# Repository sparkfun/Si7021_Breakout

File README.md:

SparkFun Humidity and Temperature Sensor Breakout - Si7021
===========================================================

[*SparkFun Humidity and Temperature Sensor Breakout - Si7021 (SEN-13763)*](https://www.sparkfun.com/products/13763)

This is a breadboard-friendly breakout board for the Si7021 temperature and humidiy sensor.

Repository Contents
-------------------
* **/Firmware** - Example code
* **/Hardware** - Eagle design files (.brd, .sch)
* **/Libraries** - Libraries for use with the Si7021
* **/Production** - Production panel files (.brd)

Documentation
--------------
* **[Library](https://github.com/sparkfun/SparkFun_Si701_Breakout_Arduino_Library)** - Arduino library for the Si7021.
* **[Hookup Guide](https://learn.sparkfun.com/tutorials/si7021-humidity-and-temperature-sensor-hookup-guide)** - Basic hookup guide for the Si7021.
* **[SparkFun Fritzing repo](https://github.com/sparkfun/Fritzing_Parts)** - Fritzing diagrams for SparkFun products.
* **[SparkFun 3D Model repo](https://github.com/sparkfun/3D_Models)** - 3D models of SparkFun products.

License Information
-------------------

This product is _**open source**_!

Please review the LICENSE.md file for license information.

If you have any questions or concerns on licensing, please contact techsupport@sparkfun.com.

Distributed as-is; no warranty is given.

- Your friends at SparkFun.

_<COLLABORATION CREDIT>_

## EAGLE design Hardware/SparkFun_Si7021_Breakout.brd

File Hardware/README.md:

SparkFun <PRODUCT NAME> Design Files
=====================================

The .sch and .brd files hare are Eagle CAD schematic and PCB design files from SparkFun Electronics.
A freeware version of Eagle can be found [here](http://www.cadsoftusa.com/download-eagle/freeware/). 

License Information
-------------------

This product is _**open source**_!

Please review the LICENSE.md file for license information.

If you have any questions or concerns on licensing, please contact techsupport@sparkfun.com.

Distributed as-is; no warranty is given.

- Your friends at SparkFun.

_<COLLABORATION CREDIT>_

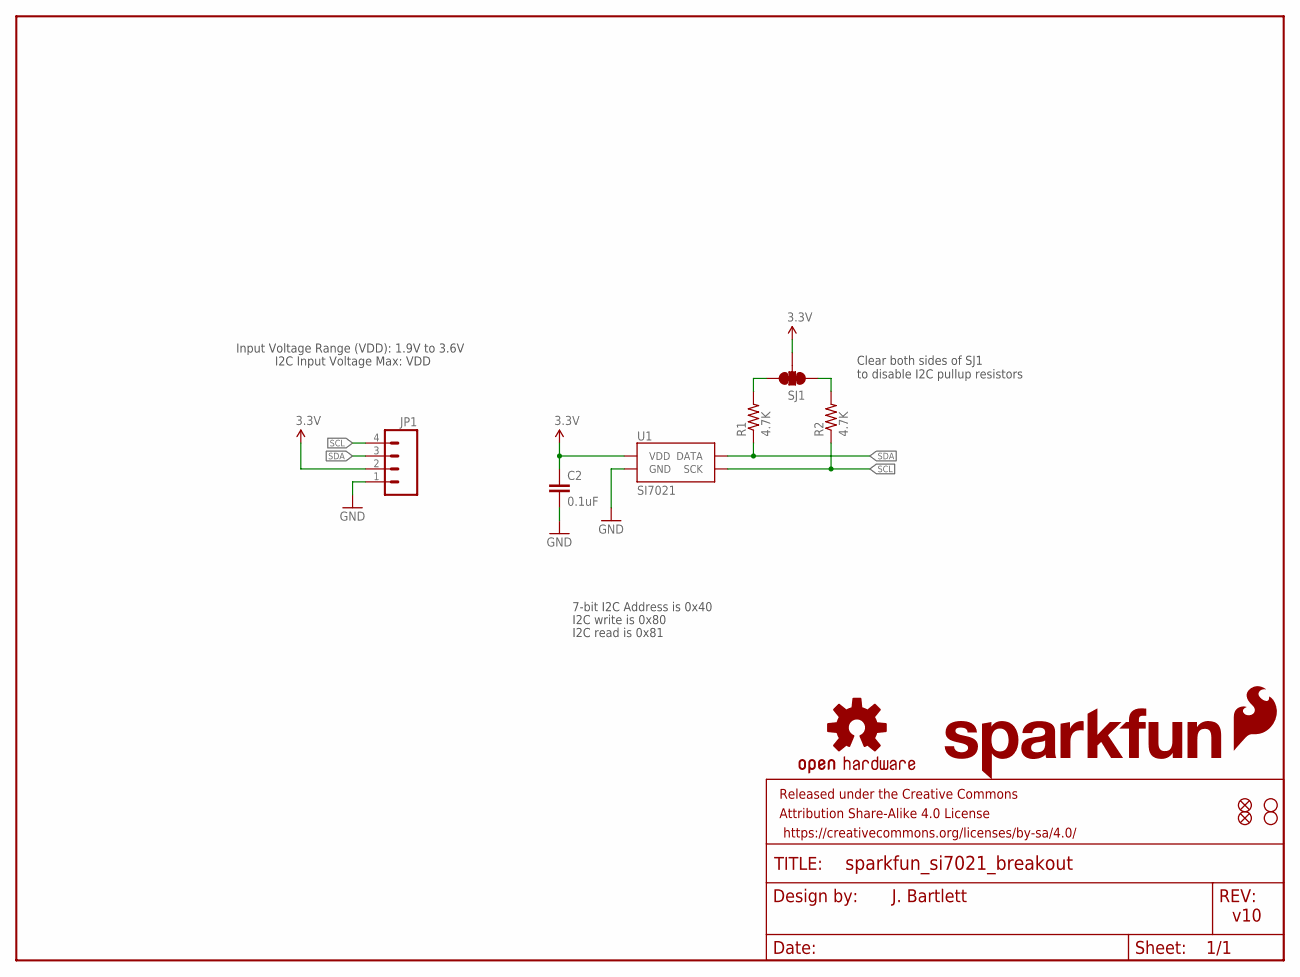
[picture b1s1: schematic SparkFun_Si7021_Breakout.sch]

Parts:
C2: 0.1uF; 0603-CAP
FRAME2: FRAME-LETTER; CREATIVE_COMMONS
JP1: M04PTH; 1X04
JP3, JP4: FIDUCIALUFIDUCIAL; MICRO-FIDUCIAL
LOGO2: OSHW-LOGOS; OSHW-LOGO-S
LOGO3: SFE_LOGO_FLAME.1_INCH; SFE_LOGO_FLAME_.1
LOGO4: SFE_LOGO_NAME.1_INCH; SFE_LOGO_NAME_.1
R1, R2: 4.7K; 0603-RES
SJ1: SOLDERJUMPER_2WAYPASTE1&2&3; SJ_3_PASTE1&2&3
STANDOFF1, STANDOFF2: STAND-OFF
U1: SI7021

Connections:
3.3V: C2.1, JP1.2, SJ1.2, U1.VDD
GND: C2.2, JP1.1, U1.GND
unnamed: R1.2, SJ1.3
unnamed: R2.2, SJ1.1
SCL: JP1.4, R2.1, U1.SCK
SDA: JP1.3, R1.1, U1.DATA

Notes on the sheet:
J. Bartlett
Clear both sides of SJ1 to disable I2C pullup resistors
7-bit I2C Address is 0x40
I2C write is 0x80
I2C read is 0x81
v10
Input Voltage Range (VDD): 1.9V to 3.6V
I2C Input Voltage Max: VDD

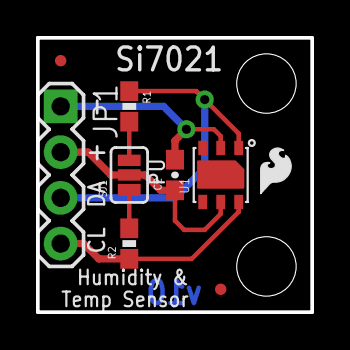
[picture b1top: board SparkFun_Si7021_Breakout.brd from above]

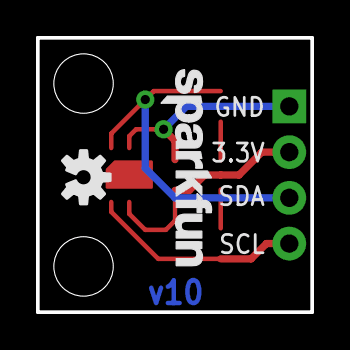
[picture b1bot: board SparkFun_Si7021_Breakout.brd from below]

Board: 2 copper layers, 15.2 x 15.2 mm, 14 parts (2 on the bottom side), 6 nets.

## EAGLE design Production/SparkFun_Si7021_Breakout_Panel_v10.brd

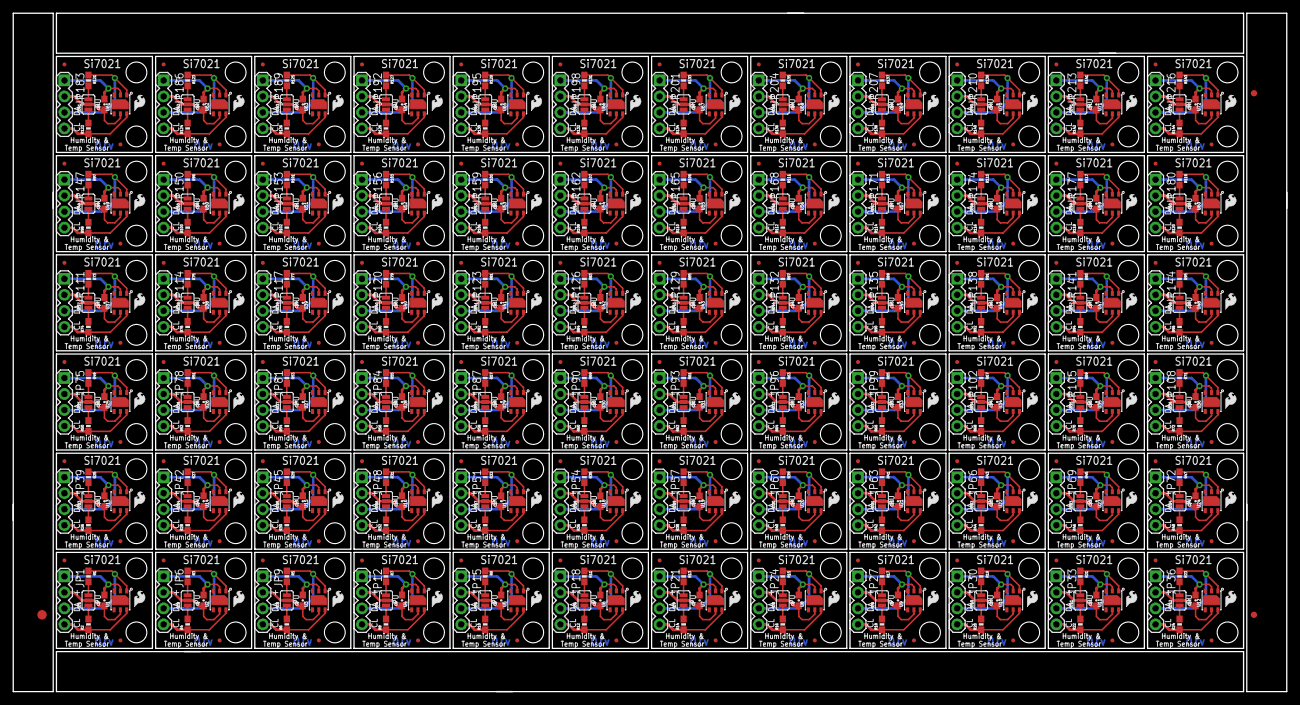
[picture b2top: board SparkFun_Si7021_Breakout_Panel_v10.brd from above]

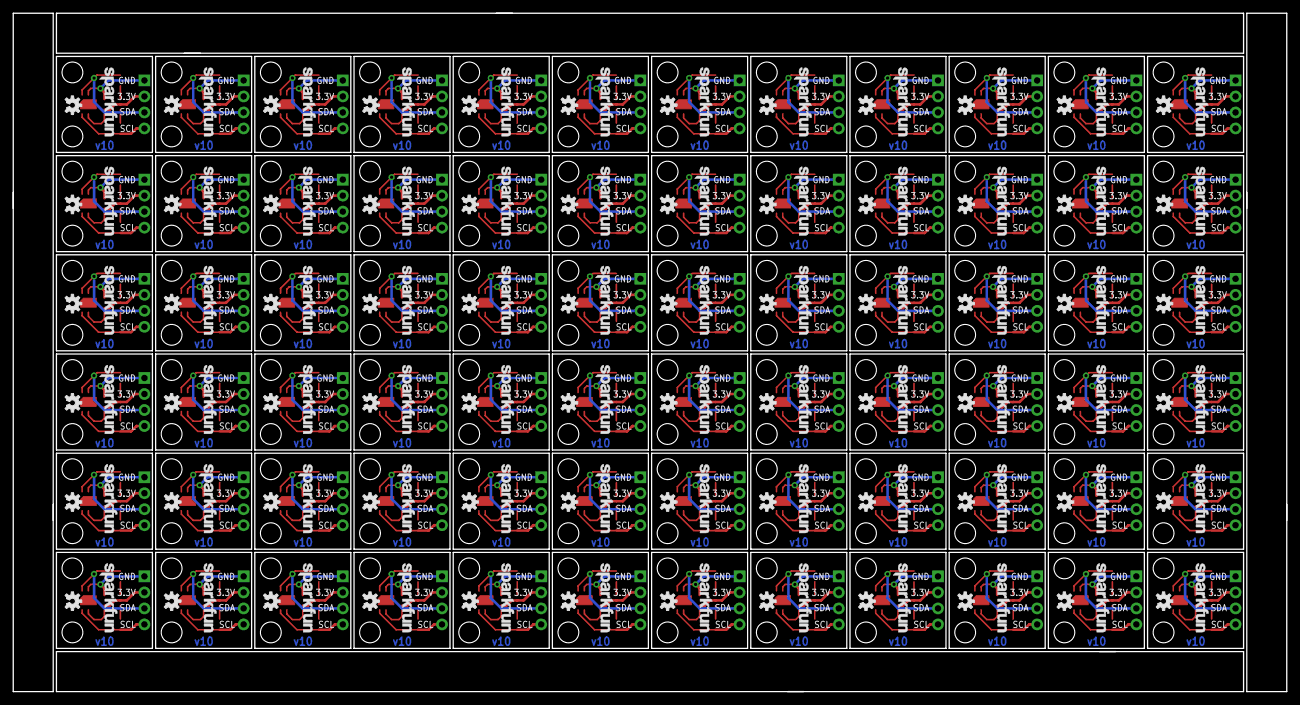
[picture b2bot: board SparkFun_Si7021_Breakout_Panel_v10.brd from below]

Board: 2 copper layers, 202.2 x 107.7 mm, 939 parts (144 on the bottom side), 432 nets.

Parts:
C1, C2, C3, C4, C5, C6, C7, C8, C9, C10, C11, C12, C13, C14, C15, C16, C17, C18, C19, C20, C21, C22, C23, C24, C25, C26, C27, C28, C29, C30, C31, C32, C33, C34, C35, C36, C37, C38, C39, C40, C41, C42, C43, C44, C45, C46, C47, C48, C49, C50, C51, C52, C53, C54, C55, C56, C57, C58, C59, C60, C61, C62, C63, C64, C65, C66, C67, C68, C69, C70, C71, C72: 0.1uF; 0603-CAP
E$1: FIDUCIAL-1.5X3
E$5, E$6: FIDUCIAL-1X2
JP1, JP6, JP9, JP12, JP15, JP18, JP21, JP24, JP27, JP30, JP33, JP36, JP39, JP42, JP45, JP48, JP51, JP54, JP57, JP60, JP63, JP66, JP69, JP72, JP75, JP78, JP81, JP84, JP87, JP90, JP93, JP96, JP99, JP102, JP105, JP108, JP111, JP114, JP117, JP120, JP123, JP126, JP129, JP132, JP135, JP138, JP141, JP144, JP147, JP150, JP153, JP156, JP159, JP162, JP165, JP168, JP171, JP174, JP177, JP180, JP183, JP186, JP189, JP192, JP195, JP198, JP201, JP204, JP207, JP210, JP213, JP216: 1X04
JP2, JP3, JP4, JP5, JP7, JP8, JP10, JP11, JP13, JP14, JP16, JP17, JP19, JP20, JP22, JP23, JP25, JP26, JP28, JP29, JP31, JP32, JP34, JP35, JP37, JP38, JP40, JP41, JP43, JP44, JP46, JP47, JP49, JP50, JP52, JP53, JP55, JP56, JP58, JP59, JP61, JP62, JP64, JP65, JP67, JP68, JP70, JP71, JP73, JP74, JP76, JP77, JP79, JP80, JP82, JP83, JP85, JP86, JP88, JP89, JP91, JP92, JP94, JP95, JP97, JP98, JP100, JP101, JP103, JP104, JP106, JP107, JP109, JP110, JP112, JP113, JP115, JP116, JP118, JP119, JP121, JP122, JP124, JP125, JP127, JP128, JP130, JP131, JP133, JP134, JP136, JP137, JP139, JP140, JP142, JP143, JP145, JP146, JP148, JP149, JP151, JP152, JP154, JP155, JP157, JP158, JP160, JP161, JP163, JP164, JP166, JP167, JP169, JP170, JP172, JP173, JP175, JP176, JP178, JP179, JP181, JP182, JP184, JP185, JP187, JP188, JP190, JP191, JP193, JP194, JP196, JP197, JP199, JP200, JP202, JP203, JP205, JP206, JP208, JP209, JP211, JP212, JP214, JP215: FIDUCIALUFIDUCIAL; MICRO-FIDUCIAL
LOGO1, LOGO2, LOGO7, LOGO10, LOGO13, LOGO16, LOGO19, LOGO22, LOGO25, LOGO28, LOGO31, LOGO34, LOGO37, LOGO40, LOGO43, LOGO46, LOGO49, LOGO52, LOGO55, LOGO58, LOGO61, LOGO64, LOGO67, LOGO70, LOGO73, LOGO76, LOGO79, LOGO82, LOGO85, LOGO88, LOGO91, LOGO94, LOGO97, LOGO100, LOGO103, LOGO106, LOGO109, LOGO112, LOGO115, LOGO118, LOGO121, LOGO124, LOGO127, LOGO130, LOGO133, LOGO136, LOGO139, LOGO142, LOGO145, LOGO148, LOGO151, LOGO154, LOGO157, LOGO160, LOGO163, LOGO166, LOGO169, LOGO172, LOGO175, LOGO178, LOGO181, LOGO184, LOGO187, LOGO190, LOGO193, LOGO196, LOGO199, LOGO202, LOGO205, LOGO208, LOGO211, LOGO214: OSHW-LOGOS; OSHW-LOGO-S
LOGO3, LOGO5, LOGO8, LOGO11, LOGO14, LOGO17, LOGO20, LOGO23, LOGO26, LOGO29, LOGO32, LOGO35, LOGO38, LOGO41, LOGO44, LOGO47, LOGO50, LOGO53, LOGO56, LOGO59, LOGO62, LOGO65, LOGO68, LOGO71, LOGO74, LOGO77, LOGO80, LOGO83, LOGO86, LOGO89, LOGO92, LOGO95, LOGO98, LOGO101, LOGO104, LOGO107, LOGO110, LOGO113, LOGO116, LOGO119, LOGO122, LOGO125, LOGO128, LOGO131, LOGO134, LOGO137, LOGO140, LOGO143, LOGO146, LOGO149, LOGO152, LOGO155, LOGO158, LOGO161, LOGO164, LOGO167, LOGO170, LOGO173, LOGO176, LOGO179, LOGO182, LOGO185, LOGO188, LOGO191, LOGO194, LOGO197, LOGO200, LOGO203, LOGO206, LOGO209, LOGO212, LOGO215: SFE_LOGO_FLAME.1_INCH; SFE_LOGO_FLAME_.1
LOGO4, LOGO6, LOGO9, LOGO12, LOGO15, LOGO18, LOGO21, LOGO24, LOGO27, LOGO30, LOGO33, LOGO36, LOGO39, LOGO42, LOGO45, LOGO48, LOGO51, LOGO54, LOGO57, LOGO60, LOGO63, LOGO66, LOGO69, LOGO72, LOGO75, LOGO78, LOGO81, LOGO84, LOGO87, LOGO90, LOGO93, LOGO96, LOGO99, LOGO102, LOGO105, LOGO108, LOGO111, LOGO114, LOGO117, LOGO120, LOGO123, LOGO126, LOGO129, LOGO132, LOGO135, LOGO138, LOGO141, LOGO144, LOGO147, LOGO150, LOGO153, LOGO156, LOGO159, LOGO162, LOGO165, LOGO168, LOGO171, LOGO174, LOGO177, LOGO180, LOGO183, LOGO186, LOGO189, LOGO192, LOGO195, LOGO198, LOGO201, LOGO204, LOGO207, LOGO210, LOGO213, LOGO216: SFE_LOGO_NAME.1_INCH; SFE_LOGO_NAME_.1
R1, R2, R3, R4, R5, R6, R7, R8, R9, R10, R11, R12, R13, R14, R15, R16, R17, R18, R19, R20, R21, R22, R23, R24, R25, R26, R27, R28, R29, R30, R31, R32, R33, R34, R35, R36, R37, R38, R39, R40, R41, R42, R43, R44, R45, R46, R47, R48, R49, R50, R51, R52, R53, R54, R55, R56, R57, R58, R59, R60, R61, R62, R63, R64, R65, R66, R67, R68, R69, R70, R71, R72, R73, R74, R75, R76, R77, R78, R79, R80, R81, R82, R83, R84, R85, R86, R87, R88, R89, R90, R91, R92, R93, R94, R95, R96, R97, R98, R99, R100, R101, R102, R103, R104, R105, R106, R107, R108, R109, R110, R111, R112, R113, R114, R115, R116, R117, R118, R119, R120, R121, R122, R123, R124, R125, R126, R127, R128, R129, R130, R131, R132, R133, R134, R135, R136, R137, R138, R139, R140, R141, R142, R143, R144: 4.7K; 0603-RES
SJ1, SJ2, SJ3, SJ4, SJ5, SJ6, SJ7, SJ8, SJ9, SJ10, SJ11, SJ12, SJ13, SJ14, SJ15, SJ16, SJ17, SJ18, SJ19, SJ20, SJ21, SJ22, SJ23, SJ24, SJ25, SJ26, SJ27, SJ28, SJ29, SJ30, SJ31, SJ32, SJ33, SJ34, SJ35, SJ36, SJ37, SJ38, SJ39, SJ40, SJ41, SJ42, SJ43, SJ44, SJ45, SJ46, SJ47, SJ48, SJ49, SJ50, SJ51, SJ52, SJ53, SJ54, SJ55, SJ56, SJ57, SJ58, SJ59, SJ60, SJ61, SJ62, SJ63, SJ64, SJ65, SJ66, SJ67, SJ68, SJ69, SJ70, SJ71, SJ72: SJ_3_PASTE1&2&3
STANDOFF1, STANDOFF2, STANDOFF3, STANDOFF4, STANDOFF5, STANDOFF6, STANDOFF7, STANDOFF8, STANDOFF9, STANDOFF10, STANDOFF11, STANDOFF12, STANDOFF13, STANDOFF14, STANDOFF15, STANDOFF16, STANDOFF17, STANDOFF18, STANDOFF19, STANDOFF20, STANDOFF21, STANDOFF22, STANDOFF23, STANDOFF24, STANDOFF25, STANDOFF26, STANDOFF27, STANDOFF28, STANDOFF29, STANDOFF30, STANDOFF31, STANDOFF32, STANDOFF33, STANDOFF34, STANDOFF35, STANDOFF36, STANDOFF37, STANDOFF38, STANDOFF39, STANDOFF40, STANDOFF41, STANDOFF42, STANDOFF43, STANDOFF44, STANDOFF45, STANDOFF46, STANDOFF47, STANDOFF48, STANDOFF49, STANDOFF50, STANDOFF51, STANDOFF52, STANDOFF53, STANDOFF54, STANDOFF55, STANDOFF56, STANDOFF57, STANDOFF58, STANDOFF59, STANDOFF60, STANDOFF61, STANDOFF62, STANDOFF63, STANDOFF64, STANDOFF65, STANDOFF66, STANDOFF67, STANDOFF68, STANDOFF69, STANDOFF70, STANDOFF71, STANDOFF72, STANDOFF73, STANDOFF74, STANDOFF75, STANDOFF76, STANDOFF77, STANDOFF78, STANDOFF79, STANDOFF80, STANDOFF81, STANDOFF82, STANDOFF83, STANDOFF84, STANDOFF85, STANDOFF86, STANDOFF87, STANDOFF88, STANDOFF89, STANDOFF90, STANDOFF91, STANDOFF92, STANDOFF93, STANDOFF94, STANDOFF95, STANDOFF96, STANDOFF97, STANDOFF98, STANDOFF99, STANDOFF100, STANDOFF101, STANDOFF102, STANDOFF103, STANDOFF104, STANDOFF105, STANDOFF106, STANDOFF107, STANDOFF108, STANDOFF109, STANDOFF110, STANDOFF111, STANDOFF112, STANDOFF113, STANDOFF114, STANDOFF115, STANDOFF116, STANDOFF117, STANDOFF118, STANDOFF119, STANDOFF120, STANDOFF121, STANDOFF122, STANDOFF123, STANDOFF124, STANDOFF125, STANDOFF126, STANDOFF127, STANDOFF128, STANDOFF129, STANDOFF130, STANDOFF131, STANDOFF132, STANDOFF133, STANDOFF134, STANDOFF135, STANDOFF136, STANDOFF137, STANDOFF138, STANDOFF139, STANDOFF140, STANDOFF141, STANDOFF142, STANDOFF143, STANDOFF144: STAND-OFF
U1, U2, U3, U4, U5, U6, U7, U8, U9, U10, U11, U12, U13, U14, U15, U16, U17, U18, U19, U20, U21, U22, U23, U24, U25, U26, U27, U28, U29, U30, U31, U32, U33, U34, U35, U36, U37, U38, U39, U40, U41, U42, U43, U44, U45, U46, U47, U48, U49, U50, U51, U52, U53, U54, U55, U56, U57, U58, U59, U60, U61, U62, U63, U64, U65, U66, U67, U68, U69, U70, U71, U72: SI7021

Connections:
3.3V: C2.1, JP1.2, SJ1.2, U1.VDD
3.3V1: C1.1, JP6.2, SJ2.2, U2.VDD
3.3V2: C3.1, JP9.2, SJ3.2, U3.VDD
3.3V3: C4.1, JP12.2, SJ4.2, U4.VDD
3.3V4: C5.1, JP15.2, SJ5.2, U5.VDD
3.3V5: C6.1, JP18.2, SJ6.2, U6.VDD
3.3V6: C7.1, JP21.2, SJ7.2, U7.VDD
3.3V7: C8.1, JP24.2, SJ8.2, U8.VDD
3.3V8: C9.1, JP27.2, SJ9.2, U9.VDD
3.3V9: C10.1, JP30.2, SJ10.2, U10.VDD
3.3V10: C11.1, JP33.2, SJ11.2, U11.VDD
3.3V11: C12.1, JP36.2, SJ12.2, U12.VDD
3.3V12: C13.1, JP39.2, SJ13.2, U13.VDD
3.3V13: C14.1, JP42.2, SJ14.2, U14.VDD
3.3V14: C15.1, JP45.2, SJ15.2, U15.VDD
3.3V15: C16.1, JP48.2, SJ16.2, U16.VDD
3.3V16: C17.1, JP51.2, SJ17.2, U17.VDD
3.3V17: C18.1, JP54.2, SJ18.2, U18.VDD
3.3V18: C19.1, JP57.2, SJ19.2, U19.VDD
3.3V19: C20.1, JP60.2, SJ20.2, U20.VDD
3.3V20: C21.1, JP63.2, SJ21.2, U21.VDD
3.3V21: C22.1, JP66.2, SJ22.2, U22.VDD
3.3V22: C23.1, JP69.2, SJ23.2, U23.VDD
3.3V23: C24.1, JP72.2, SJ24.2, U24.VDD
3.3V24: C25.1, JP75.2, SJ25.2, U25.VDD
3.3V25: C26.1, JP78.2, SJ26.2, U26.VDD
3.3V26: C27.1, JP81.2, SJ27.2, U27.VDD
3.3V27: C28.1, JP84.2, SJ28.2, U28.VDD
3.3V28: C29.1, JP87.2, SJ29.2, U29.VDD
3.3V29: C30.1, JP90.2, SJ30.2, U30.VDD
3.3V30: C31.1, JP93.2, SJ31.2, U31.VDD
3.3V31: C32.1, JP96.2, SJ32.2, U32.VDD
3.3V32: C33.1, JP99.2, SJ33.2, U33.VDD
3.3V33: C34.1, JP102.2, SJ34.2, U34.VDD
3.3V34: C35.1, JP105.2, SJ35.2, U35.VDD
3.3V35: C36.1, JP108.2, SJ36.2, U36.VDD
3.3V36: C37.1, JP111.2, SJ37.2, U37.VDD
3.3V37: C38.1, JP114.2, SJ38.2, U38.VDD
3.3V38: C39.1, JP117.2, SJ39.2, U39.VDD
3.3V39: C40.1, JP120.2, SJ40.2, U40.VDD
3.3V40: C41.1, JP123.2, SJ41.2, U41.VDD
3.3V41: C42.1, JP126.2, SJ42.2, U42.VDD
3.3V42: C43.1, JP129.2, SJ43.2, U43.VDD
3.3V43: C44.1, JP132.2, SJ44.2, U44.VDD
3.3V44: C45.1, JP135.2, SJ45.2, U45.VDD
3.3V45: C46.1, JP138.2, SJ46.2, U46.VDD
3.3V46: C47.1, JP141.2, SJ47.2, U47.VDD
3.3V47: C48.1, JP144.2, SJ48.2, U48.VDD
3.3V48: C49.1, JP147.2, SJ49.2, U49.VDD
3.3V49: C50.1, JP150.2, SJ50.2, U50.VDD
3.3V50: C51.1, JP153.2, SJ51.2, U51.VDD
3.3V51: C52.1, JP156.2, SJ52.2, U52.VDD
3.3V52: C53.1, JP159.2, SJ53.2, U53.VDD
3.3V53: C54.1, JP162.2, SJ54.2, U54.VDD
3.3V54: C55.1, JP165.2, SJ55.2, U55.VDD
3.3V55: C56.1, JP168.2, SJ56.2, U56.VDD
3.3V56: C57.1, JP171.2, SJ57.2, U57.VDD
3.3V57: C58.1, JP174.2, SJ58.2, U58.VDD
3.3V58: C59.1, JP177.2, SJ59.2, U59.VDD
3.3V59: C60.1, JP180.2, SJ60.2, U60.VDD
3.3V60: C61.1, JP183.2, SJ61.2, U61.VDD
3.3V61: C62.1, JP186.2, SJ62.2, U62.VDD
3.3V62: C63.1, JP189.2, SJ63.2, U63.VDD
3.3V63: C64.1, JP192.2, SJ64.2, U64.VDD
3.3V64: C65.1, JP195.2, SJ65.2, U65.VDD
3.3V65: C66.1, JP198.2, SJ66.2, U66.VDD
3.3V66: C67.1, JP201.2, SJ67.2, U67.VDD
3.3V67: C68.1, JP204.2, SJ68.2, U68.VDD
3.3V68: C69.1, JP207.2, SJ69.2, U69.VDD
3.3V69: C70.1, JP210.2, SJ70.2, U70.VDD
3.3V70: C71.1, JP213.2, SJ71.2, U71.VDD
3.3V71: C72.1, JP216.2, SJ72.2, U72.VDD
GND: C2.2, JP1.1, U1.GND
GND1: C1.2, JP6.1, U2.GND
GND2: C3.2, JP9.1, U3.GND
GND3: C4.2, JP12.1, U4.GND
GND4: C5.2, JP15.1, U5.GND
GND5: C6.2, JP18.1, U6.GND
GND6: C7.2, JP21.1, U7.GND
GND7: C8.2, JP24.1, U8.GND
GND8: C9.2, JP27.1, U9.GND
GND9: C10.2, JP30.1, U10.GND
GND10: C11.2, JP33.1, U11.GND
GND11: C12.2, JP36.1, U12.GND
GND12: C13.2, JP39.1, U13.GND
GND13: C14.2, JP42.1, U14.GND
GND14: C15.2, JP45.1, U15.GND
GND15: C16.2, JP48.1, U16.GND
GND16: C17.2, JP51.1, U17.GND
GND17: C18.2, JP54.1, U18.GND
GND18: C19.2, JP57.1, U19.GND
GND19: C20.2, JP60.1, U20.GND
GND20: C21.2, JP63.1, U21.GND
GND21: C22.2, JP66.1, U22.GND
GND22: C23.2, JP69.1, U23.GND
GND23: C24.2, JP72.1, U24.GND
GND24: C25.2, JP75.1, U25.GND
GND25: C26.2, JP78.1, U26.GND
GND26: C27.2, JP81.1, U27.GND
GND27: C28.2, JP84.1, U28.GND
GND28: C29.2, JP87.1, U29.GND
GND29: C30.2, JP90.1, U30.GND
GND30: C31.2, JP93.1, U31.GND
GND31: C32.2, JP96.1, U32.GND
GND32: C33.2, JP99.1, U33.GND
GND33: C34.2, JP102.1, U34.GND
GND34: C35.2, JP105.1, U35.GND
GND35: C36.2, JP108.1, U36.GND
GND36: C37.2, JP111.1, U37.GND
GND37: C38.2, JP114.1, U38.GND
GND38: C39.2, JP117.1, U39.GND
GND39: C40.2, JP120.1, U40.GND
GND40: C41.2, JP123.1, U41.GND
GND41: C42.2, JP126.1, U42.GND
GND42: C43.2, JP129.1, U43.GND
GND43: C44.2, JP132.1, U44.GND
GND44: C45.2, JP135.1, U45.GND
GND45: C46.2, JP138.1, U46.GND
GND46: C47.2, JP141.1, U47.GND
GND47: C48.2, JP144.1, U48.GND
GND48: C49.2, JP147.1, U49.GND
GND49: C50.2, JP150.1, U50.GND
GND50: C51.2, JP153.1, U51.GND
GND51: C52.2, JP156.1, U52.GND
GND52: C53.2, JP159.1, U53.GND
GND53: C54.2, JP162.1, U54.GND
GND54: C55.2, JP165.1, U55.GND
GND55: C56.2, JP168.1, U56.GND
GND56: C57.2, JP171.1, U57.GND
GND57: C58.2, JP174.1, U58.GND
GND58: C59.2, JP177.1, U59.GND
GND59: C60.2, JP180.1, U60.GND
GND60: C61.2, JP183.1, U61.GND
GND61: C62.2, JP186.1, U62.GND
GND62: C63.2, JP189.1, U63.GND
GND63: C64.2, JP192.1, U64.GND
GND64: C65.2, JP195.1, U65.GND
GND65: C66.2, JP198.1, U66.GND
GND66: C67.2, JP201.1, U67.GND
GND67: C68.2, JP204.1, U68.GND
GND68: C69.2, JP207.1, U69.GND
GND69: C70.2, JP210.1, U70.GND
GND70: C71.2, JP213.1, U71.GND
GND71: C72.2, JP216.1, U72.GND
unnamed: R1.2, SJ1.3
unnamed: R2.2, SJ1.1
unnamed: R3.2, SJ2.3
unnamed: R4.2, SJ2.1
unnamed: R5.2, SJ3.3
unnamed: R6.2, SJ3.1
unnamed: R7.2, SJ4.3
unnamed: R8.2, SJ4.1
unnamed: R9.2, SJ5.3
unnamed: R10.2, SJ5.1
unnamed: R11.2, SJ6.3
unnamed: R12.2, SJ6.1
unnamed: R13.2, SJ7.3
unnamed: R14.2, SJ7.1
unnamed: R15.2, SJ8.3
unnamed: R16.2, SJ8.1
unnamed: R17.2, SJ9.3
unnamed: R18.2, SJ9.1
unnamed: R19.2, SJ10.3
unnamed: R20.2, SJ10.1
unnamed: R21.2, SJ11.3
unnamed: R22.2, SJ11.1
unnamed: R23.2, SJ12.3
unnamed: R24.2, SJ12.1
unnamed: R25.2, SJ13.3
unnamed: R26.2, SJ13.1
unnamed: R27.2, SJ14.3
unnamed: R28.2, SJ14.1
unnamed: R29.2, SJ15.3
unnamed: R30.2, SJ15.1
unnamed: R31.2, SJ16.3
unnamed: R32.2, SJ16.1
unnamed: R33.2, SJ17.3
unnamed: R34.2, SJ17.1
unnamed: R35.2, SJ18.3
unnamed: R36.2, SJ18.1
unnamed: R37.2, SJ19.3
unnamed: R38.2, SJ19.1
unnamed: R39.2, SJ20.3
unnamed: R40.2, SJ20.1
unnamed: R41.2, SJ21.3
unnamed: R42.2, SJ21.1
unnamed: R43.2, SJ22.3
unnamed: R44.2, SJ22.1
unnamed: R45.2, SJ23.3
unnamed: R46.2, SJ23.1
unnamed: R47.2, SJ24.3
unnamed: R48.2, SJ24.1
unnamed: R49.2, SJ25.3
unnamed: R50.2, SJ25.1
unnamed: R51.2, SJ26.3
unnamed: R52.2, SJ26.1
unnamed: R53.2, SJ27.3
unnamed: R54.2, SJ27.1
unnamed: R55.2, SJ28.3
unnamed: R56.2, SJ28.1
unnamed: R57.2, SJ29.3
unnamed: R58.2, SJ29.1
unnamed: R59.2, SJ30.3
unnamed: R60.2, SJ30.1
unnamed: R61.2, SJ31.3
unnamed: R62.2, SJ31.1
unnamed: R63.2, SJ32.3
unnamed: R64.2, SJ32.1
unnamed: R65.2, SJ33.3
unnamed: R66.2, SJ33.1
unnamed: R67.2, SJ34.3
unnamed: R68.2, SJ34.1
unnamed: R69.2, SJ35.3
unnamed: R70.2, SJ35.1
unnamed: R71.2, SJ36.3
unnamed: R72.2, SJ36.1
unnamed: R73.2, SJ37.3
unnamed: R74.2, SJ37.1
unnamed: R75.2, SJ38.3
unnamed: R76.2, SJ38.1
unnamed: R77.2, SJ39.3
unnamed: R78.2, SJ39.1
unnamed: R79.2, SJ40.3
unnamed: R80.2, SJ40.1
unnamed: R81.2, SJ41.3
unnamed: R82.2, SJ41.1
unnamed: R83.2, SJ42.3
unnamed: R84.2, SJ42.1
unnamed: R85.2, SJ43.3
unnamed: R86.2, SJ43.1
unnamed: R87.2, SJ44.3
unnamed: R88.2, SJ44.1
unnamed: R89.2, SJ45.3
unnamed: R90.2, SJ45.1
unnamed: R91.2, SJ46.3
unnamed: R92.2, SJ46.1
unnamed: R93.2, SJ47.3
unnamed: R94.2, SJ47.1
unnamed: R95.2, SJ48.3
unnamed: R96.2, SJ48.1
unnamed: R97.2, SJ49.3
unnamed: R98.2, SJ49.1
unnamed: R99.2, SJ50.3
unnamed: R100.2, SJ50.1
unnamed: R101.2, SJ51.3
unnamed: R102.2, SJ51.1
unnamed: R103.2, SJ52.3
unnamed: R104.2, SJ52.1
unnamed: R105.2, SJ53.3
unnamed: R106.2, SJ53.1
unnamed: R107.2, SJ54.3
unnamed: R108.2, SJ54.1
unnamed: R109.2, SJ55.3
unnamed: R110.2, SJ55.1
unnamed: R111.2, SJ56.3
unnamed: R112.2, SJ56.1
unnamed: R113.2, SJ57.3
unnamed: R114.2, SJ57.1
unnamed: R115.2, SJ58.3
unnamed: R116.2, SJ58.1
unnamed: R117.2, SJ59.3
unnamed: R118.2, SJ59.1
unnamed: R119.2, SJ60.3
unnamed: R120.2, SJ60.1
unnamed: R121.2, SJ61.3
unnamed: R122.2, SJ61.1
unnamed: R123.2, SJ62.3
unnamed: R124.2, SJ62.1
unnamed: R125.2, SJ63.3
unnamed: R126.2, SJ63.1
unnamed: R127.2, SJ64.3
unnamed: R128.2, SJ64.1
unnamed: R129.2, SJ65.3
unnamed: R130.2, SJ65.1
unnamed: R131.2, SJ66.3
unnamed: R132.2, SJ66.1
unnamed: R133.2, SJ67.3
unnamed: R134.2, SJ67.1
unnamed: R135.2, SJ68.3
unnamed: R136.2, SJ68.1
unnamed: R137.2, SJ69.3
unnamed: R138.2, SJ69.1
unnamed: R139.2, SJ70.3
unnamed: R140.2, SJ70.1
unnamed: R141.2, SJ71.3
unnamed: R142.2, SJ71.1
unnamed: R143.2, SJ72.3
unnamed: R144.2, SJ72.1
SCL: JP1.4, R2.1, U1.SCK
SCL1: JP6.4, R4.1, U2.SCK
SCL2: JP9.4, R6.1, U3.SCK
SCL3: JP12.4, R8.1, U4.SCK
SCL4: JP15.4, R10.1, U5.SCK
SCL5: JP18.4, R12.1, U6.SCK
SCL6: JP21.4, R14.1, U7.SCK
SCL7: JP24.4, R16.1, U8.SCK
SCL8: JP27.4, R18.1, U9.SCK
SCL9: JP30.4, R20.1, U10.SCK
SCL10: JP33.4, R22.1, U11.SCK
SCL11: JP36.4, R24.1, U12.SCK
SCL12: JP39.4, R26.1, U13.SCK
SCL13: JP42.4, R28.1, U14.SCK
SCL14: JP45.4, R30.1, U15.SCK
SCL15: JP48.4, R32.1, U16.SCK
SCL16: JP51.4, R34.1, U17.SCK
SCL17: JP54.4, R36.1, U18.SCK
SCL18: JP57.4, R38.1, U19.SCK
SCL19: JP60.4, R40.1, U20.SCK
SCL20: JP63.4, R42.1, U21.SCK
SCL21: JP66.4, R44.1, U22.SCK
SCL22: JP69.4, R46.1, U23.SCK
SCL23: JP72.4, R48.1, U24.SCK
SCL24: JP75.4, R50.1, U25.SCK
SCL25: JP78.4, R52.1, U26.SCK
SCL26: JP81.4, R54.1, U27.SCK
SCL27: JP84.4, R56.1, U28.SCK
SCL28: JP87.4, R58.1, U29.SCK
SCL29: JP90.4, R60.1, U30.SCK
SCL30: JP93.4, R62.1, U31.SCK
SCL31: JP96.4, R64.1, U32.SCK
SCL32: JP99.4, R66.1, U33.SCK
SCL33: JP102.4, R68.1, U34.SCK
SCL34: JP105.4, R70.1, U35.SCK
SCL35: JP108.4, R72.1, U36.SCK
SCL36: JP111.4, R74.1, U37.SCK
SCL37: JP114.4, R76.1, U38.SCK
SCL38: JP117.4, R78.1, U39.SCK
SCL39: JP120.4, R80.1, U40.SCK
SCL40: JP123.4, R82.1, U41.SCK
SCL41: JP126.4, R84.1, U42.SCK
SCL42: JP129.4, R86.1, U43.SCK
SCL43: JP132.4, R88.1, U44.SCK
SCL44: JP135.4, R90.1, U45.SCK
SCL45: JP138.4, R92.1, U46.SCK
SCL46: JP141.4, R94.1, U47.SCK
SCL47: JP144.4, R96.1, U48.SCK
SCL48: JP147.4, R98.1, U49.SCK
SCL49: JP150.4, R100.1, U50.SCK
SCL50: JP153.4, R102.1, U51.SCK
SCL51: JP156.4, R104.1, U52.SCK
SCL52: JP159.4, R106.1, U53.SCK
SCL53: JP162.4, R108.1, U54.SCK
SCL54: JP165.4, R110.1, U55.SCK
SCL55: JP168.4, R112.1, U56.SCK
SCL56: JP171.4, R114.1, U57.SCK
SCL57: JP174.4, R116.1, U58.SCK
SCL58: JP177.4, R118.1, U59.SCK
SCL59: JP180.4, R120.1, U60.SCK
SCL60: JP183.4, R122.1, U61.SCK
SCL61: JP186.4, R124.1, U62.SCK
SCL62: JP189.4, R126.1, U63.SCK
SCL63: JP192.4, R128.1, U64.SCK
SCL64: JP195.4, R130.1, U65.SCK
SCL65: JP198.4, R132.1, U66.SCK
SCL66: JP201.4, R134.1, U67.SCK
SCL67: JP204.4, R136.1, U68.SCK
SCL68: JP207.4, R138.1, U69.SCK
SCL69: JP210.4, R140.1, U70.SCK
SCL70: JP213.4, R142.1, U71.SCK
SCL71: JP216.4, R144.1, U72.SCK
SDA: JP1.3, R1.1, U1.DATA
SDA1: JP6.3, R3.1, U2.DATA
SDA2: JP9.3, R5.1, U3.DATA
SDA3: JP12.3, R7.1, U4.DATA
SDA4: JP15.3, R9.1, U5.DATA
SDA5: JP18.3, R11.1, U6.DATA
SDA6: JP21.3, R13.1, U7.DATA
SDA7: JP24.3, R15.1, U8.DATA
SDA8: JP27.3, R17.1, U9.DATA
SDA9: JP30.3, R19.1, U10.DATA
SDA10: JP33.3, R21.1, U11.DATA
SDA11: JP36.3, R23.1, U12.DATA
SDA12: JP39.3, R25.1, U13.DATA
SDA13: JP42.3, R27.1, U14.DATA
SDA14: JP45.3, R29.1, U15.DATA
SDA15: JP48.3, R31.1, U16.DATA
SDA16: JP51.3, R33.1, U17.DATA
SDA17: JP54.3, R35.1, U18.DATA
SDA18: JP57.3, R37.1, U19.DATA
SDA19: JP60.3, R39.1, U20.DATA
SDA20: JP63.3, R41.1, U21.DATA
SDA21: JP66.3, R43.1, U22.DATA
SDA22: JP69.3, R45.1, U23.DATA
SDA23: JP72.3, R47.1, U24.DATA
SDA24: JP75.3, R49.1, U25.DATA
SDA25: JP78.3, R51.1, U26.DATA
SDA26: JP81.3, R53.1, U27.DATA
SDA27: JP84.3, R55.1, U28.DATA
SDA28: JP87.3, R57.1, U29.DATA
SDA29: JP90.3, R59.1, U30.DATA
SDA30: JP93.3, R61.1, U31.DATA
SDA31: JP96.3, R63.1, U32.DATA
SDA32: JP99.3, R65.1, U33.DATA
SDA33: JP102.3, R67.1, U34.DATA
SDA34: JP105.3, R69.1, U35.DATA
SDA35: JP108.3, R71.1, U36.DATA
SDA36: JP111.3, R73.1, U37.DATA
SDA37: JP114.3, R75.1, U38.DATA
SDA38: JP117.3, R77.1, U39.DATA
SDA39: JP120.3, R79.1, U40.DATA
SDA40: JP123.3, R81.1, U41.DATA
SDA41: JP126.3, R83.1, U42.DATA
SDA42: JP129.3, R85.1, U43.DATA
SDA43: JP132.3, R87.1, U44.DATA
SDA44: JP135.3, R89.1, U45.DATA
SDA45: JP138.3, R91.1, U46.DATA
SDA46: JP141.3, R93.1, U47.DATA
SDA47: JP144.3, R95.1, U48.DATA
SDA48: JP147.3, R97.1, U49.DATA
SDA49: JP150.3, R99.1, U50.DATA
SDA50: JP153.3, R101.1, U51.DATA
SDA51: JP156.3, R103.1, U52.DATA
SDA52: JP159.3, R105.1, U53.DATA
SDA53: JP162.3, R107.1, U54.DATA
SDA54: JP165.3, R109.1, U55.DATA
SDA55: JP168.3, R111.1, U56.DATA
SDA56: JP171.3, R113.1, U57.DATA
SDA57: JP174.3, R115.1, U58.DATA
SDA58: JP177.3, R117.1, U59.DATA
SDA59: JP180.3, R119.1, U60.DATA
SDA60: JP183.3, R121.1, U61.DATA
SDA61: JP186.3, R123.1, U62.DATA
SDA62: JP189.3, R125.1, U63.DATA
SDA63: JP192.3, R127.1, U64.DATA
SDA64: JP195.3, R129.1, U65.DATA
SDA65: JP198.3, R131.1, U66.DATA
SDA66: JP201.3, R133.1, U67.DATA
SDA67: JP204.3, R135.1, U68.DATA
SDA68: JP207.3, R137.1, U69.DATA
SDA69: JP210.3, R139.1, U70.DATA
SDA70: JP213.3, R141.1, U71.DATA
SDA71: JP216.3, R143.1, U72.DATA

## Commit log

2015-10-26 Initial Commit
    Adding .brd and .sch files plus a few extras like datasheet
2015-10-27 Changes from Hardware Review with Toni
    Lots of minor changes brought up during Toni’s Hardware review. See
    repo issues for more details.
2015-10-27 Changes from Hardware Review with Marshall
    very minor changes - moved via, bumped trace with up near header, minor
    spelling error on sch.
2015-11-03 Pushing minor changes from first QC check
    Caps and resistors needed prod ID, version should be v01, not v10,
    altered center pad on Si7021 IC to have 50% paste instead of 100%.
2015-11-09 Updated TSTOP on Si7021 IC Package
2015-12-17 Changed version number on BRD and SCH to v10
2015-12-18 created panel v10
2016-01-28 increased paste on triple jumper
2016-05-05 Final repo cleanup
    Added Arduino Library and firmware. Also cleaning up all readies, etc.
2017-04-27 change type from void to bool for begin()
    begin() only returns text via Serial.println() but nothing which could be catch by some logic in the calling function. turning it into a bool allows the calling function to react on the result.
2017-07-21 Updated License information to be consistent
2017-07-21 Updating license information
2017-07-21 Updating library files
2017-08-08 Updating ire.requestFrom() function to remove wait
2018-05-22 Added "return true" to begin function.
2018-05-22 Added "return false" for completion (it returns null otherwise, so it does not seem right anyway).
2018-07-09 Improved Readability
    Changed from literal to TEMP_PREV as defined in header file.
2018-07-18 Improved Efficiency
    Reduced delay when waiting for measurement in accordance with max conversion time identified on datasheet. Reduced delay from 100ms to 23ms.
2018-12-14 Removing library from board repo

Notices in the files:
parts and their libraries:
SparkFun-Electromechanical: Licensing: CC v3.0 Share-Alike You are welcome to use this library for commercial purposes.
SparkFun-Aesthetics: Released under the Creative Commons Attribution Share-Alike 4.0 License
SparkFun-Aesthetics: https://creativecommons.org/licenses/by-sa/4.0
